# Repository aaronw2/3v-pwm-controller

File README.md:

# 3v-pwm-controller
An Arduino M0 PWM controller with 3 mosfets designed to perform PWM on 3V or 5V with a 3A 3V supply

This PWM controller provides 3 PWM channels designed to sink current.
Due to the back EMF protection diodes, do not exceed 5v.

The 3V supply is capable of providing up to 3A of current and is designed
to be powered by a 5V supply.

Each PWM channel should be able to handle at least 3A of current at up to 5V.
The MOSFETs are rated at over 8A each.

J1:
1: +5V
2: +5V
3: PWM0 connected to PA00
4: PA08
5: PWM1 connected to PA01
6: PA09
7: PWM2 connected to PA02
8: PA10
9: +3V
10: +3V
11: GND
12: GND

J2:
1: D_P (D+) USB signal
2: D_N (D-) USB signal
3: PA22
4: PA21
5: PA19
6: PA18
7: +3V
8: GND

J3:
1: +5V
2: GND

SW1: Reset

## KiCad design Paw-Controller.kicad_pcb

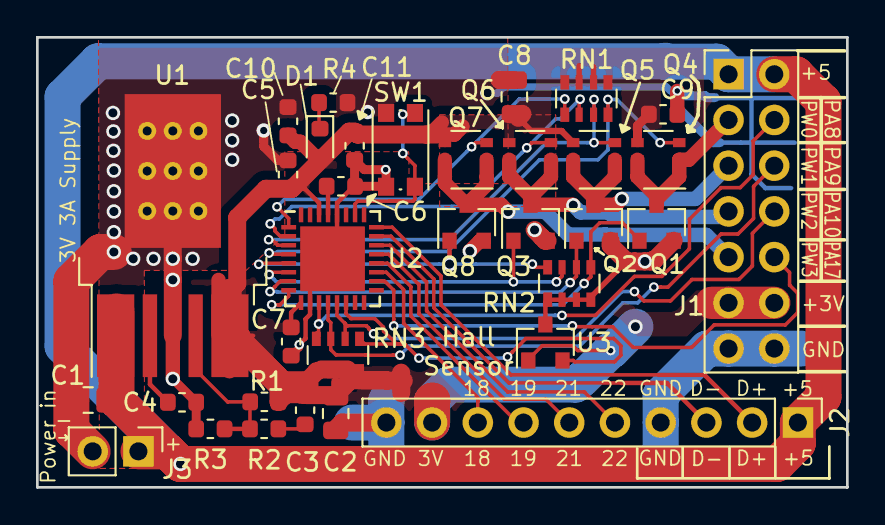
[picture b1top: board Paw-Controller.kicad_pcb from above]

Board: 2 copper layers, 45.0 x 25.0 mm, 34 parts (0 on the bottom side), 32 nets.

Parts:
C1: 22uF; C_0805_2012Metric
C2, C8: 47uF; C_0805_2012Metric
C3: 91pF; C_0603_1608Metric
C4: 0.022uF; C_0603_1608Metric
C5, C6, C7, C10: 1uF; C_0603_1608Metric
C9, C11: 0.1uF; C_0603_1608Metric
D1: LED; LED_0603_1608Metric
J1: Conn_02x07_Odd_Even; PinHeader_2x07_P2.54mm_Vertical
J2: Conn_01x10; PinHeader_1x10_P2.54mm_Vertical
J3: Conn_01x02; PinHeader_1x02_P2.54mm_Vertical
Q1, Q2, Q3, Q8: DMN1019USN; SOT-23
Q4, Q5, Q6, Q7: SI3407DV-T1-GE3; TSOP-6_1.65x3.05mm_P0.95mm
R1: 82.5K; R_0603_1608Metric
R2: 1.27K; R_0603_1608Metric
R3: 30K; R_0603_1608Metric
R4: 330; R_0603_1608Metric
RN1, RN2: 100K; R_Array_Convex_4x0603
RN3: 10K; R_Array_Convex_4x0603
SW1: SW_SPST_KMR2
U1: LMZ10503; TO-PMOD-7_TabPin4
U2: ATSAMD21E18A-AF; QFN-32-1EP_5x5mm_P0.5mm_EP3.6x3.6mm
U3: DRV5032FCDBZT; SOT-23

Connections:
+3V3: C2.1, C3.1, C5.1, C7.1, C8.1, C9.1, C10.1, C11.1, D1.2, J1.11, J1.12, J2.9, Q4.4, Q5.4, Q6.4, Q7.4, R1.1, RN1.5, RN1.6, RN1.7, RN1.8, RN3.5, RN3.6, RN3.7, RN3.8, U1.6, U1.7, U2.9, U2.30, U3.1
+5V: C1.1, J1.1, J1.2, J2.1, J3.1, U1.1, U1.2
/D_N: J2.3, U2.23
/D_P: J2.2, U2.24
/PA00: Q7.3, RN1.1, U2.1
/PA01: Q6.3, RN1.2, U2.2
/PA02: Q5.3, RN1.3, U2.3
/PA03: Q4.3, RN1.4, U2.4
/PA04: Q8.1, RN2.8, U2.5
/PA05: Q3.1, RN2.7, U2.6
/PA06: Q2.1, RN2.6, U2.7
/PA07: Q1.1, RN2.5, U2.8
/PA08: J1.4, RN3.4, U2.11
/PA09: J1.6, RN3.3, U2.12
/PA10: J1.8, RN3.2, U2.13
/PA11: RN3.1, U2.14, U3.2
/PA17: J1.10, U2.18
/PA18: J2.8, U2.19
/PA19: J2.7, U2.20
/PA21: J2.6, U2.21
/PA22: J2.5, U2.22
/PWM0: J1.3, Q1.3, Q4.1, Q4.2, Q4.5, Q4.6
/PWM1: J1.5, Q2.3, Q5.1, Q5.2, Q5.5, Q5.6
/PWM2: J1.7, Q3.3, Q6.1, Q6.2, Q6.5, Q6.6
/PWM3: J1.9, Q7.1, Q7.2, Q7.5, Q7.6, Q8.3
GND: C1.2, C2.2, C4.2, C5.2, C6.2, C7.2, C8.2, C9.2, C10.2, C11.2, J1.13, J1.14, J2.4, J2.10, J3.2, Q1.2, Q2.2, Q3.2, Q8.2, R3.2, R4.1, RN2.1, RN2.2, RN2.3, RN2.4, SW1.1, U1.4, U2.10, U2.28, U2.33, U3.3
unnamed: C3.2, R2.1
unnamed: C4.1, U1.3
unnamed: C6.1, U2.29
unnamed: D1.1, R4.2
unnamed: R1.2, R2.2, R3.1, U1.5
unnamed: SW1.2, U2.26

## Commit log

2018-10-15 Initial checkin of Arduino M0 based PWM controller.
    This PWM controller provides 3 PWM channels designed to sink current.
    Due to the back EMF protection diodes, do not exceed 5v.
    The 3V supply is capable of providing up to 3A of current and is designed
    to be powered by a 5V supply.
    Each PWM channel should be able to handle at least 3A of current at up to 5V.
    The MOSFETs are rated at over 8A each.
2018-10-15 Added missing PWM labels.
2018-10-16 Version 2.0 converts each PWM channel to use an H-bridge.
    This allows the controller to be able to drive a 3V brushless motor. The
    M0 processor is capable of generating the timing for the motors, though at
    this time I don't know if it works with 6 GPIO pins or only with three.
    Six was chosen so that a PWMs can be set to a high impedence state. This
    is useful in the case where multiple brushed motors are attached between either
    +3v or ground and the PWM pin, though the alternative is to just pull the PWM
2019-01-26 Fixed solder mask clearance.
2019-01-30 Fixed P-CH mosfets and changed to more readily available mosfet.
2019-01-30 Add another push/pull channel
    This adds a 4th push/pull channel and exports PA17 to J1.
    Due to the increase in board size, two more pins were added to J2,
    an additional +5 and ground pin for USB.
    Updated to version 2.2.0
2019-02-05 Fixed silkscreen and solder mask.

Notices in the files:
Paw-Controller.kicad_pcb:
Copyright © 2018 by Aaron Williams
Copyright © 2019 by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
